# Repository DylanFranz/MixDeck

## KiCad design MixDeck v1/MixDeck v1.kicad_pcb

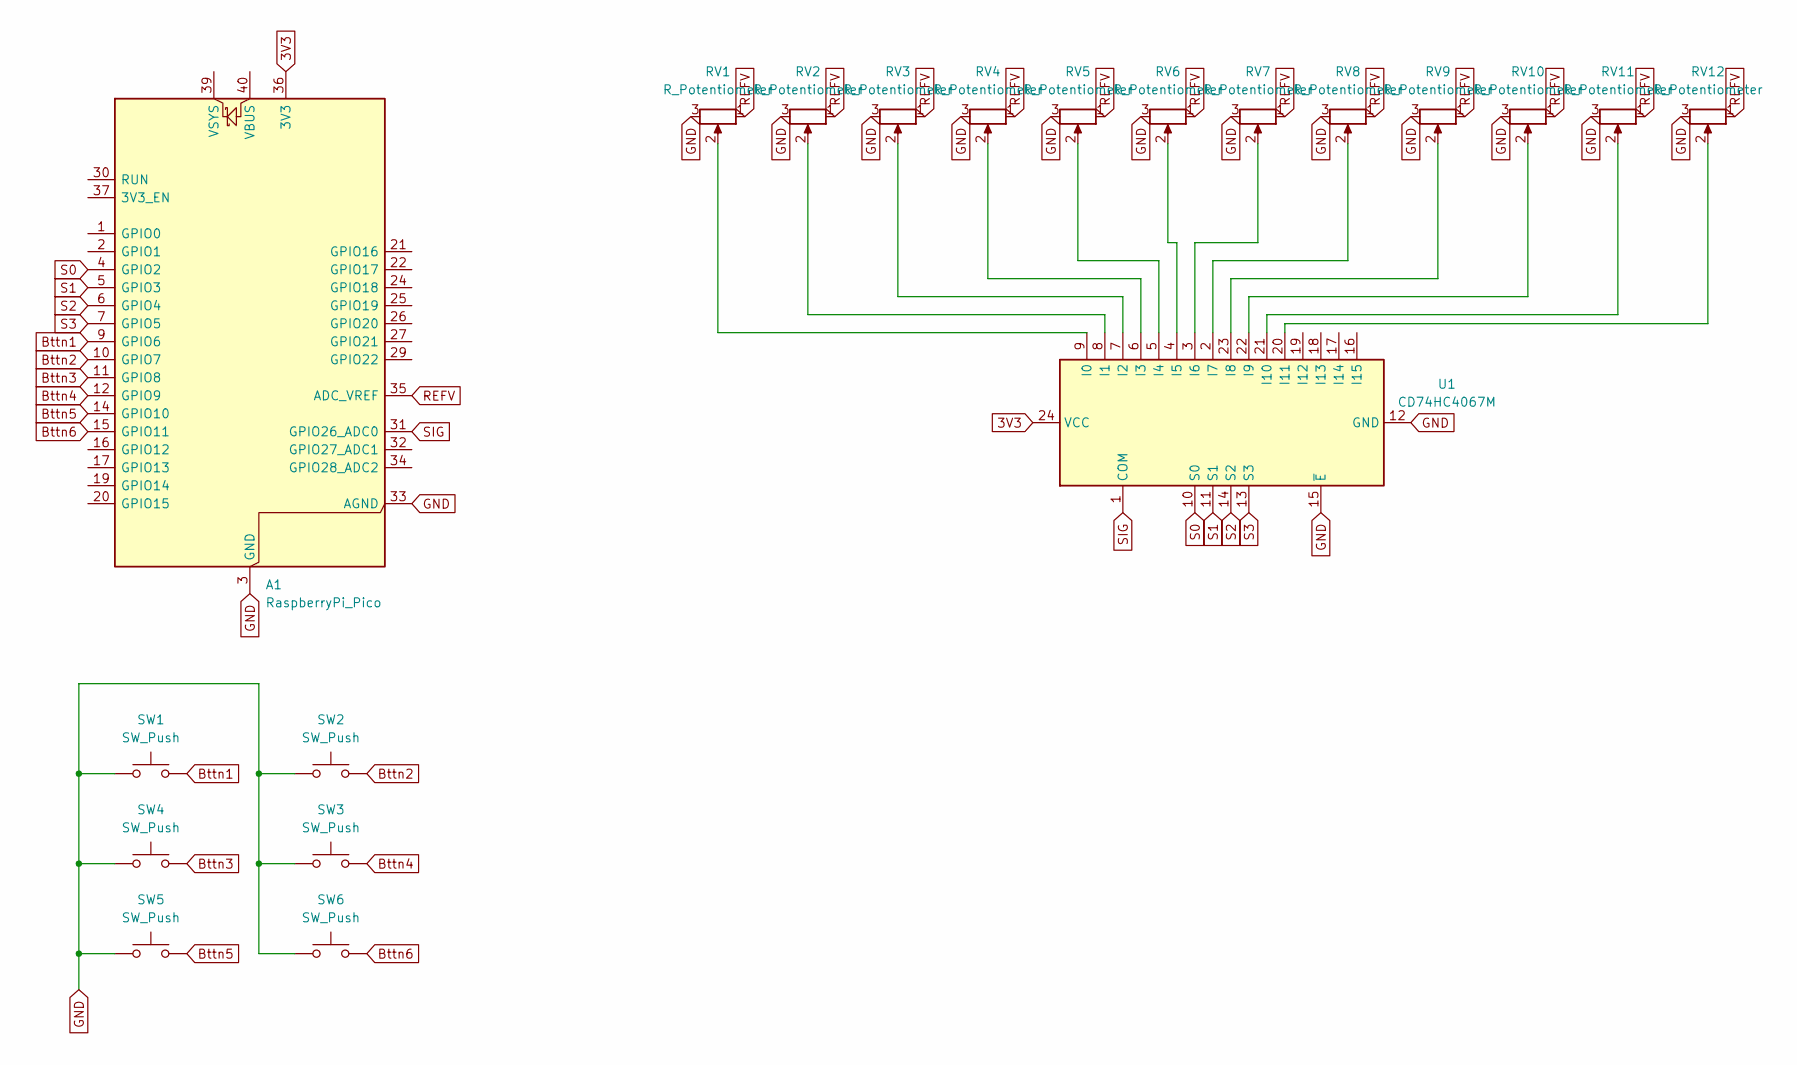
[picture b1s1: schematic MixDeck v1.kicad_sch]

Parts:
A1: RaspberryPi_Pico; RaspberryPi_Pico_Common_Unspecified
RV1, RV2, RV3, RV4, RV5, RV6, RV7, RV8, RV9, RV10, RV11, RV12: R_Potentiometer; PTB01432010BPA103
SW1, SW2, SW3, SW4, SW5, SW6: SW_Push; SW_Cherry_MX_1.00u_PCB
U1: CD74HC4067M; SOIC-24W_7.5x15.4mm_P1.27mm

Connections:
3V3: A1.36 (3V3), U1.24 (VCC)
Bttn1: A1.9 (GPIO6), SW1.2
Bttn2: A1.10 (GPIO7), SW2.2
Bttn3: A1.11 (GPIO8), SW4.2
Bttn4: A1.12 (GPIO9), SW3.2
Bttn5: A1.14 (GPIO10), SW5.2
Bttn6: A1.15 (GPIO11), SW6.2
GND: A1.3 (GND), A1.8 (GND), A1.13 (GND), A1.18 (GND), A1.23 (GND), A1.28 (GND), A1.33 (AGND), A1.38 (GND), RV1.3, RV2.3, RV3.3, RV4.3, RV5.3, RV6.3, RV7.3, RV8.3, RV9.3, RV10.3, RV11.3, RV12.3, SW1.1, SW2.1, SW3.1, SW4.1, SW5.1, SW6.1, U1.12 (GND), U1.15 (~E)
unnamed: RV1.2, U1.9 (I0)
unnamed: RV2.2, U1.8 (I1)
unnamed: RV3.2, U1.7 (I2)
unnamed: RV4.2, U1.6 (I3)
unnamed: RV5.2, U1.5 (I4)
unnamed: RV6.2, U1.4 (I5)
unnamed: RV7.2, U1.3 (I6)
unnamed: RV8.2, U1.2 (I7)
unnamed: RV9.2, U1.23 (I8)
unnamed: RV10.2, U1.22 (I9)
unnamed: RV11.2, U1.21 (I10)
unnamed: RV12.2, U1.20 (I11)
REFV: A1.35 (ADC_VREF), RV1.1, RV2.1, RV3.1, RV4.1, RV5.1, RV6.1, RV7.1, RV8.1, RV9.1, RV10.1, RV11.1, RV12.1
S0: A1.4 (GPIO2), U1.10 (S0)
S1: A1.5 (GPIO3), U1.11 (S1)
S2: A1.6 (GPIO4), U1.14 (S2)
S3: A1.7 (GPIO5), U1.13 (S3)
SIG: A1.31 (GPIO26_ADC0), U1.1 (COM)

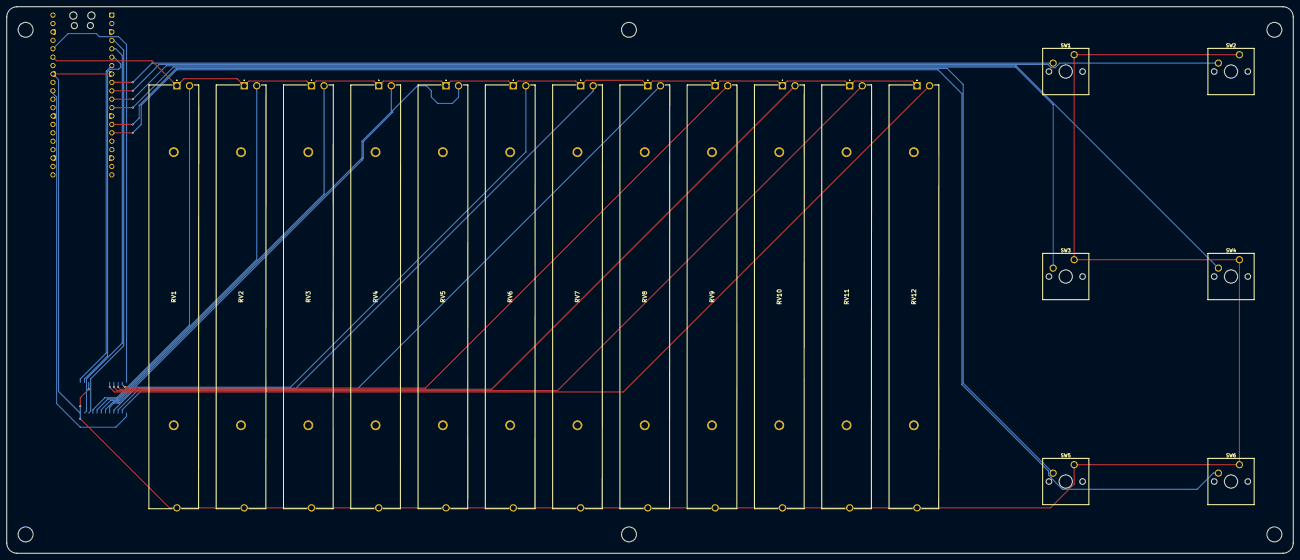
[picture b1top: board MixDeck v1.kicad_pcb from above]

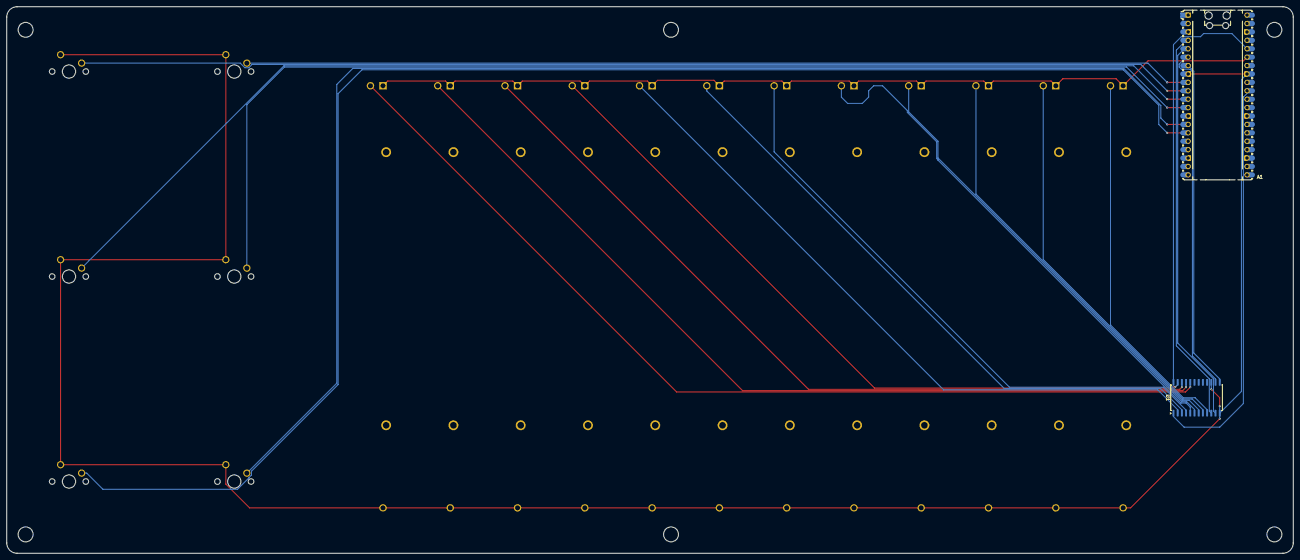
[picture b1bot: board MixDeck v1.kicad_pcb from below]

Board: 2 copper layers, 388.6 x 165.1 mm, 20 parts (2 on the bottom side), 26 nets.

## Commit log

2025-07-03 initial schematic
2025-07-08 first complete
